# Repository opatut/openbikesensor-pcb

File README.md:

# OpenBikeSensor PCB

Dieses Repository enthält die offiziellen PCBs des OpenBikeSensor Projektes.
Sie sind in der freien Software [KiCad](https://www.kicad.org/) erstellt und
können damit modifiziert werden.

## Versionen

### OpenBikeSensor

Dies ist der Standard-OpenBikeSensor als eigenständiges Gerät, hergestellt aus
vielen fertig verfügbaren Modulen (ESP32 Devkit, GPS, SD-Karten-Modul,
Ultraschallsensor-Module, ...).

Die aktuelle Versionsnummer des OpenBikeSensor PCB ist `1.0.0-alpha.1`.

* [Gerber Download (Generic)](./OpenBikeSensor/generated/Manufacturers/Generic/OpenBikeSensor-gerber_modern_zip.zip)
* [Gerber Download (JLCPCB)](./OpenBikeSensor/generated/Manufacturers/JLCPCB/OpenBikeSensor-JLCPCB.zip)
* [Schaltplan, PDF](./OpenBikeSensor/generated/OpenBikeSensor-schematic.pdf)
* [Bestückungsplan, HTML](./OpenBikeSensor/generated/OpenBikeSensor-ibom.html)

### OpenBikeSensor Lite

In naher Zukunft werden wir hier auch die PCB-Dateien des *OpenBikeSensor Lite*
veröffentlichen. Dies ist ein reduzierter Hardwareaufbau, in welchem nur der
ESP32, die zwei Sensormodule und ein Button enthalten sind, und welcher im
Zusammenspiel mit einem Smartphone die restlichen Daten sammeln kann. Dieses
Projekt ist zur Zeit in der Entwicklung und hoffentlich in der ersten
Jahreshälfte 2023 benutzbar.

### OpenBikeSensor Pro

Diese Variante des OpenBikeSensor ist ein vollständiger Nachbau aller
relevanter Teile der vorher als Modul gelieferten Funktionen in einer eigenen
Schaltung, und ist komplett maschinenbestückt bestellbar. Dies macht das Gerät
teurer und komplizierter herstellen zu lassen, aber es ist ein wesentlich
geringerer Eigenaufwand zur Fertigstellung ohne Löten elektronischer Module
nötig. Dieses Projekt is zur Zeit in der Entwicklung und hoffentlich im Laufe
des Jahres 2023 benutzbar.

### OpenBikeSensor Display

Dieses Projekt enthält die Platine für das neue kompakte Display mit Platine
und aufgelötetem Taster.

## Bestellung bei Platinenherstellern

Ein Export der Projektdateien als "Gerber-Files" liegt im jeweiligen
Projektordner vor. Die meisten Hersteller von Platinen bieten einen
Online-Konfigurator an, in den diese Dateien hochgeladen werden können, und
welcher dann auch eine Vorschau bietet. In der Regel sollten diese Exports für
alle Hersteller funktionieren, die Anforderungen an die Genauigkeit der
Produktion sind relativ gering.

Die Standardeinstellungen für die Platine sind in der Regel vollkommen
ausreichend, das ist üblicherweise ein 2-Layer Board mit einfachem Surface
Finish (HASL) in 1.6mm Stärke (FR-4) und 1oz Kupferstärke. Bessere Optionen (z.
B. ENIG) sind möglich, aber nicht nötig. Die Einstellungen können nach Belieben
angepasst werden, insbesondere ästhetische Aspekte wie die Farbe der Boards.

Einige Hersteller (z. B. Aisler) können die KiCad-Dateien direkt importieren,
hier muss nur die `.kicad_pcb` Datei ausgewählt werden, diese enthält alle
Informationen des Designs.

Bei manchen Herstellern (z. B. JLCPCB) wird die Bestellnummer auf jedes Board
aufgedruckt, für einen kleinen Mehrbetrag kann dies vermieden werden. Gerade
bei größeren Bestellungen fällt diese Gebühr kaum ins Gewicht und ist sehr zu
empfehlen.

## Lizenz

Die eigenen Inhalte dieses Repositories sind lizensiert unter den Bedingungen
der GNU Lesser General Public License. Eine Kopie der Lizenz befindet sich in der
Datei `LICENSE` in diesem Verzeichnis.

Nicht unter diese Lizenz fallen:

* Die folgenden Dateien, welche leichte Modifikationen von Standard-Footprints
  der KiCad-Bibliothek sind und somit unter der entsprechende Lizenz
  ([CC-BY-SA 4.0 mit Modifikationen](https://www.kicad.org/libraries/license/))
  stehen:
    - `libs/OpenBikeSensor.pretty/CP_Radial_D4.0mm_P1.50mm.kicad_mod`
    - `libs/OpenBikeSensor.pretty/Connector_1x02.kicad_mod`
    - `libs/OpenBikeSensor.pretty/Connector_1x04.kicad_mod`
    - `libs/OpenBikeSensor.pretty/Connector_1x05_Display.kicad_mod`
    - `libs/OpenBikeSensor.pretty/Connector_1x06.kicad_mod`

## Update der Exportdateien

Die Dateien in `generated` können mit
[KiBot](https://github.com/INTI-CMNB/KiBot) automatisch aktualisiert werden.
Eine Konfigurationsdatei liegt im jeweiligen Projektverzeichnis vor. Ein
Ausführen von `kibot` im entsprechenden Unterverzeichnis (z. B. `cd
OpenBikeSensor`) erstellt alle Exportdateien neu. Bitte checke nur solche
Dateien in git ein, welche du in deinem Commit auch inhaltlich verändert hast
(z. B. den PDF Schaltplanexport wenn der Schaltplan verändert wurde, aber nicht
wenn nur das PCB Änderungen hat).

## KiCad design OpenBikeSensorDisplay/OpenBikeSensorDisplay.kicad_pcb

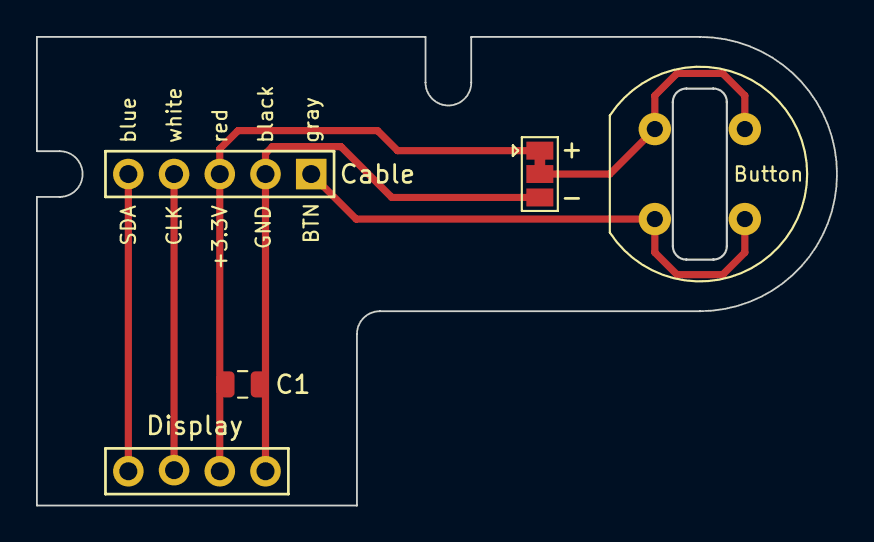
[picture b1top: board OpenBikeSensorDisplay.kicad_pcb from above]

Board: 2 copper layers, 44.4 x 26.0 mm, 5 parts (0 on the bottom side), 6 nets.

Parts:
C1: 22u; C_0805_2012Metric
J1: Display Module; PinSocket_1x04_P2.54mm_Vertical
J2: Cable; PinSocket_1x05_P2.54mm_Vertical
JP1: Button Mode Select; SolderJumper-3_P1.3mm_Bridged12_Pad1.0x1.5mm
SW1: SW_Push; SW_PUSH-12mm

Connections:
/+3.3V: J1.2, J2.3, JP1.1 (A)
/BTN: J2.1, SW1.2
/BTN_REF: JP1.2 (C), SW1.1
/CLK: J1.3, J2.4
/GND: J1.1, J2.2, JP1.3 (B)
/SDA: J1.4, J2.5

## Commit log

2022-07-24 OBS Lite v0.1.1
2022-07-24 Lite: use 3D model of sensors
2022-07-26 lite: Add button, add GND on voltage pin, change pinout to same as normal OBS
2022-11-24 wip: display
